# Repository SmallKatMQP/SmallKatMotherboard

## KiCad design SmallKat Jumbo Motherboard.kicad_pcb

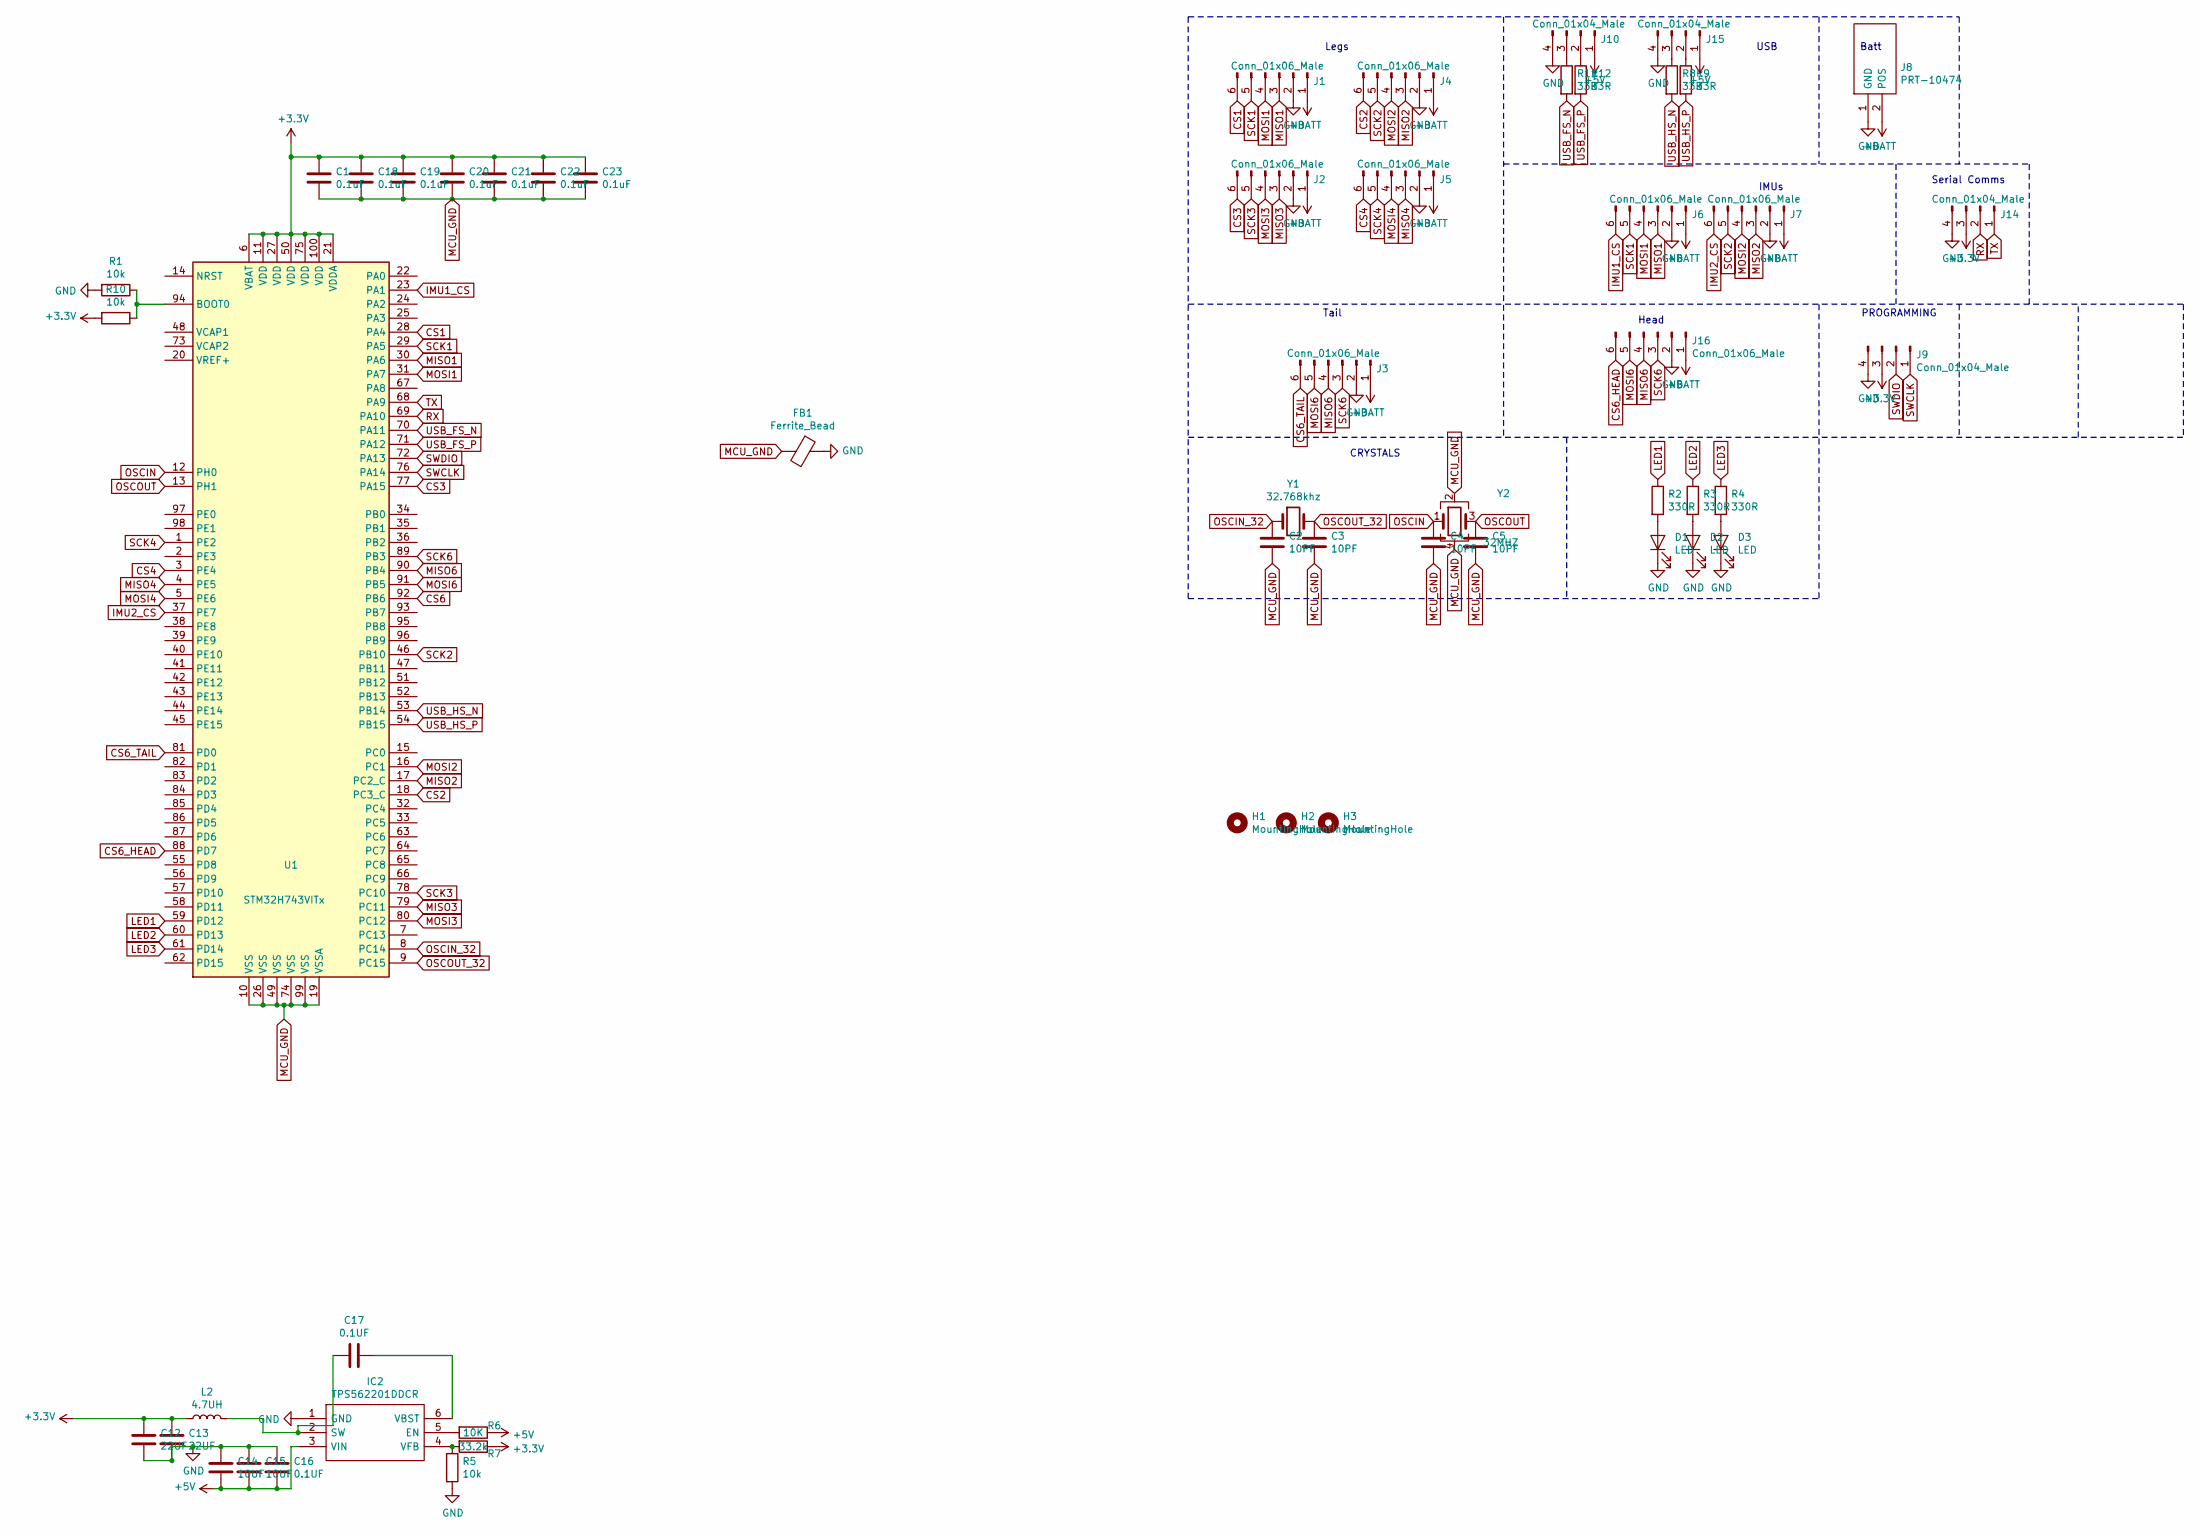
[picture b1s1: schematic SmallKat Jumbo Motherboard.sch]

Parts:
C1, C18, C19, C20, C21, C22, C23: 0.1uF; C_0402_1005Metric
C2, C3, C4, C5: 10PF; C_0402_1005Metric
C12, C13: 22UF; C_0805_2012Metric
C14, C15: 10UF; C_0805_2012Metric
C16: 0.1UF; C_0805_2012Metric
C17: 0.1UF; C_0402_1005Metric
D1, D2, D3: LED; LED_0603_1608Metric
FB1: Ferrite_Bead; L_0805_2012Metric; Part Number 742792040‎
H1, H2, H3: MountingHole; MountingHole_3.2mm_M3
IC2: TPS562201DDCR; SOT95P280X110-6N; Manufacturer_Part_Number TPS562201DDCR
J1, J2, J3, J4, J5, J6, J7, J16: Conn_01x06_Male; Molex_CLIK-Mate_502443-0670_1x06-1MP_P2.00mm_Vertical
J8: PRT-10474; XT60; Manufacturer_Part_Number PRT-10474; Mouser Part Number 474-PRT-10474
J9, J10, J14, J15: Conn_01x04_Male; Molex_CLIK-Mate_502443-0470_1x04-1MP_P2.00mm_Vertical
L2: 4.7UH; L_0805_2012Metric_Pad1.15x1.40mm_HandSolder; Part Number 74479776247
R1, R5, R10: 10k; R_0402_1005Metric
R2, R3, R4: 330R; R_0402_1005Metric
R6: 10K; R_0402_1005Metric
R7: 33.2k; R_0402_1005Metric
R8, R9, R11, R12: 33R; R_0402_1005Metric
U1: STM32H743VITx; LQFP-100_14x14mm_P0.5mm
Y1: 32.768khz; Crystal_SMD_2012-2Pin_2.0x1.2mm
Y2: 32MHZ; Crystal_SMD_2016-4Pin_2.0x1.6mm

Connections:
+3V3: C1.1, C12.1, C13.1, C18.1, C19.1, C20.1, C21.1, C22.1, C23.1, J9.3, J14.3, L2.1, R7.1, R10.2, U1.6 (VBAT), U1.11 (VDD), U1.21 (VDDA), U1.27 (VDD), U1.50 (VDD), U1.75 (VDD), U1.100 (VDD)
+5V: C14.2, C15.2, C16.2, IC2.3 (VIN), J10.1, J15.1, R6.1
+BATT: J1.1, J2.1, J3.1, J4.1, J5.1, J6.1, J7.1, J8.2 (POS), J16.1
CS1: J1.6, U1.28 (PA4)
CS2: J4.6, U1.18 (PC3_C)
CS3: J2.6, U1.77 (PA15)
CS4: J5.6, U1.3 (PE4)
CS6: U1.92 (PB6)
CS6_HEAD: J16.6, U1.88 (PD7)
CS6_TAIL: J3.6, U1.81 (PD0)
GND: C12.2, C13.2, C14.1, C15.1, C16.1, D1.1 (K), D2.1 (K), D3.1 (K), FB1.1, IC2.1 (GND), J1.2, J2.2, J3.2, J4.2, J5.2, J6.2, J7.2, J8.1 (GND), J9.4, J10.4, J14.4, J15.4, J16.2, R1.2, R5.2
IMU1_CS: J6.6, U1.23 (PA1)
IMU2_CS: J7.6, U1.37 (PE7)
LED1: R2.1, U1.59 (PD12)
LED2: R3.1, U1.60 (PD13)
LED3: R4.1, U1.61 (PD14)
MCU_GND: C1.2, C2.2, C3.2, C4.2, C5.2, C18.2, C19.2, C20.2, C21.2, C22.2, C23.2, FB1.2, U1.10 (VSS), U1.19 (VSSA), U1.26 (VSS), U1.49 (VSS), U1.74 (VSS), U1.99 (VSS), Y2.2, Y2.4
MISO1: J1.3, J6.3, U1.30 (PA6)
MISO2: J4.3, J7.3, U1.17 (PC2_C)
MISO3: J2.3, U1.79 (PC11)
MISO4: J5.3, U1.4 (PE5)
MISO6: J3.4, J16.4, U1.90 (PB4)
MOSI1: J1.4, J6.4, U1.31 (PA7)
MOSI2: J4.4, J7.4, U1.16 (PC1)
MOSI3: J2.4, U1.80 (PC12)
MOSI4: J5.4, U1.5 (PE6)
MOSI6: J3.5, J16.5, U1.91 (PB5)
unnamed: C17.1, IC2.6 (VBST)
unnamed: C17.2, IC2.2 (SW), L2.2
unnamed: D1.2 (A), R2.2
unnamed: D2.2 (A), R3.2
unnamed: D3.2 (A), R4.2
unnamed: IC2.4 (VFB), R5.1, R7.2
unnamed: IC2.5 (EN), R6.2
unnamed: J10.2, R12.1
unnamed: J10.3, R11.1
unnamed: J15.2, R9.1
unnamed: J15.3, R8.1
unnamed: R1.1, R10.1, U1.94 (BOOT0)
OSCIN: C4.1, U1.12 (PH0), Y2.1
OSCIN_32: C2.1, U1.8 (PC14), Y1.1
OSCOUT: C5.1, U1.13 (PH1), Y2.3
OSCOUT_32: C3.1, U1.9 (PC15), Y1.2
RX: J14.2, U1.69 (PA10)
SCK1: J1.5, J6.5, U1.29 (PA5)
SCK2: J4.5, J7.5, U1.46 (PB10)
SCK3: J2.5, U1.78 (PC10)
SCK4: J5.5, U1.1 (PE2)
SCK6: J3.3, J16.3, U1.89 (PB3)
SWCLK: J9.1, U1.76 (PA14)
SWDIO: J9.2, U1.72 (PA13)
TX: J14.1, U1.68 (PA9)
USB_FS_N: R11.2, U1.70 (PA11)
USB_FS_P: R12.2, U1.71 (PA12)
USB_HS_N: R8.2, U1.53 (PB14)
USB_HS_P: R9.2, U1.54 (PB15)

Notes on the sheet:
Legs
Tail
IMUs
Batt
PROGRAMMING
CRYSTALS
Serial Comms
USB
Head

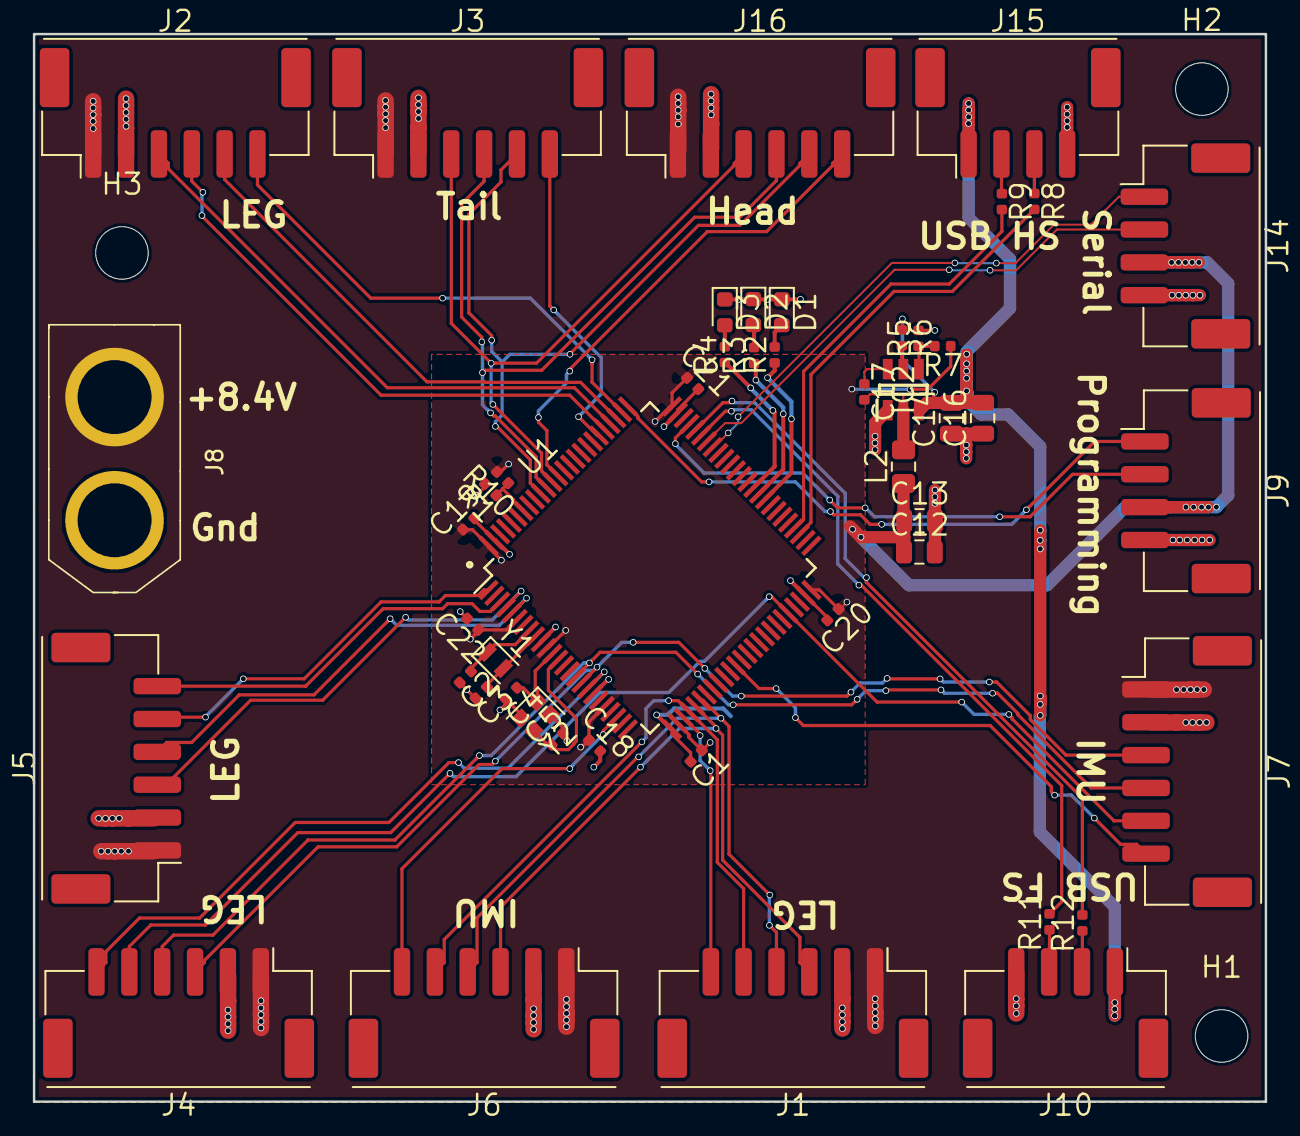
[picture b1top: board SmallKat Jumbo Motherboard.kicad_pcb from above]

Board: 4 copper layers, 75.0 x 65.0 mm, 52 parts (1 on the bottom side), 55 nets.

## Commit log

2018-08-24 Rev 1
2018-08-27 Changed footprints
2018-08-27 Reloaded planes
2018-08-27 Added mounting holes
2018-10-24 fixed pinout
2019-02-08 Rev 2
2019-02-08 Updated xt-60 plug footprint
2019-02-08 Removed fles and added updated gerbers
